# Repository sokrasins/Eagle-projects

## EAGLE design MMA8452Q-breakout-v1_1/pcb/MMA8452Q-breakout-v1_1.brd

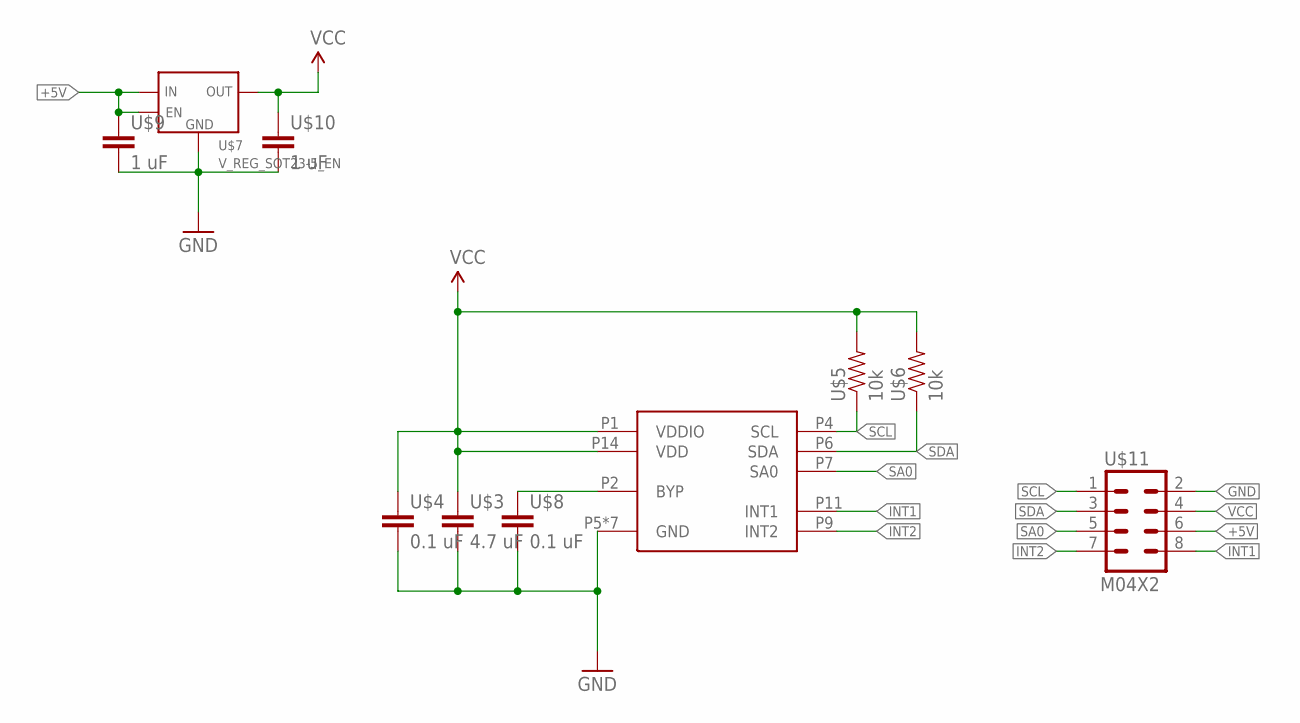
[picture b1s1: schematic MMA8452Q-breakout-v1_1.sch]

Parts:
U$2: MMA_8452; QFN-16-MMA
U$3: 4.7 uF; CAP-0603
U$4, U$8: 0.1 uF; CAP-0603
U$5, U$6: 10k; RES-0603
U$7: V_REG_SOT23-5_EN; SOT23-5
U$9, U$10: 1 uF; CAP-0603
U$11: M04X2; 2X4

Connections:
+5V: U$7.1 (IN), U$7.3 (EN), U$9.1, U$11.6
BYP: U$2.P2 (BYP), U$8.1
GND: U$2.P5 (GND), U$2.P8 (GND), U$2.P10 (GND), U$2.P12 (GND), U$2.P13 (GND), U$2.P15 (GND), U$2.P16 (GND), U$3.2, U$4.2, U$7.2 (GND), U$8.2, U$9.2, U$10.2, U$11.2
INT1: U$2.P11 (INT1), U$11.8
INT2: U$2.P9 (INT2), U$11.7
SA0: U$2.P7 (SA0), U$11.5
SCL: U$2.P4 (SCL), U$5.1, U$11.1
SDA: U$2.P6 (SDA), U$6.1, U$11.3
VCC: U$2.P1 (VDDIO), U$2.P14 (VDD), U$3.1, U$4.1, U$5.2, U$6.2, U$7.5 (OUT), U$10.1, U$11.4

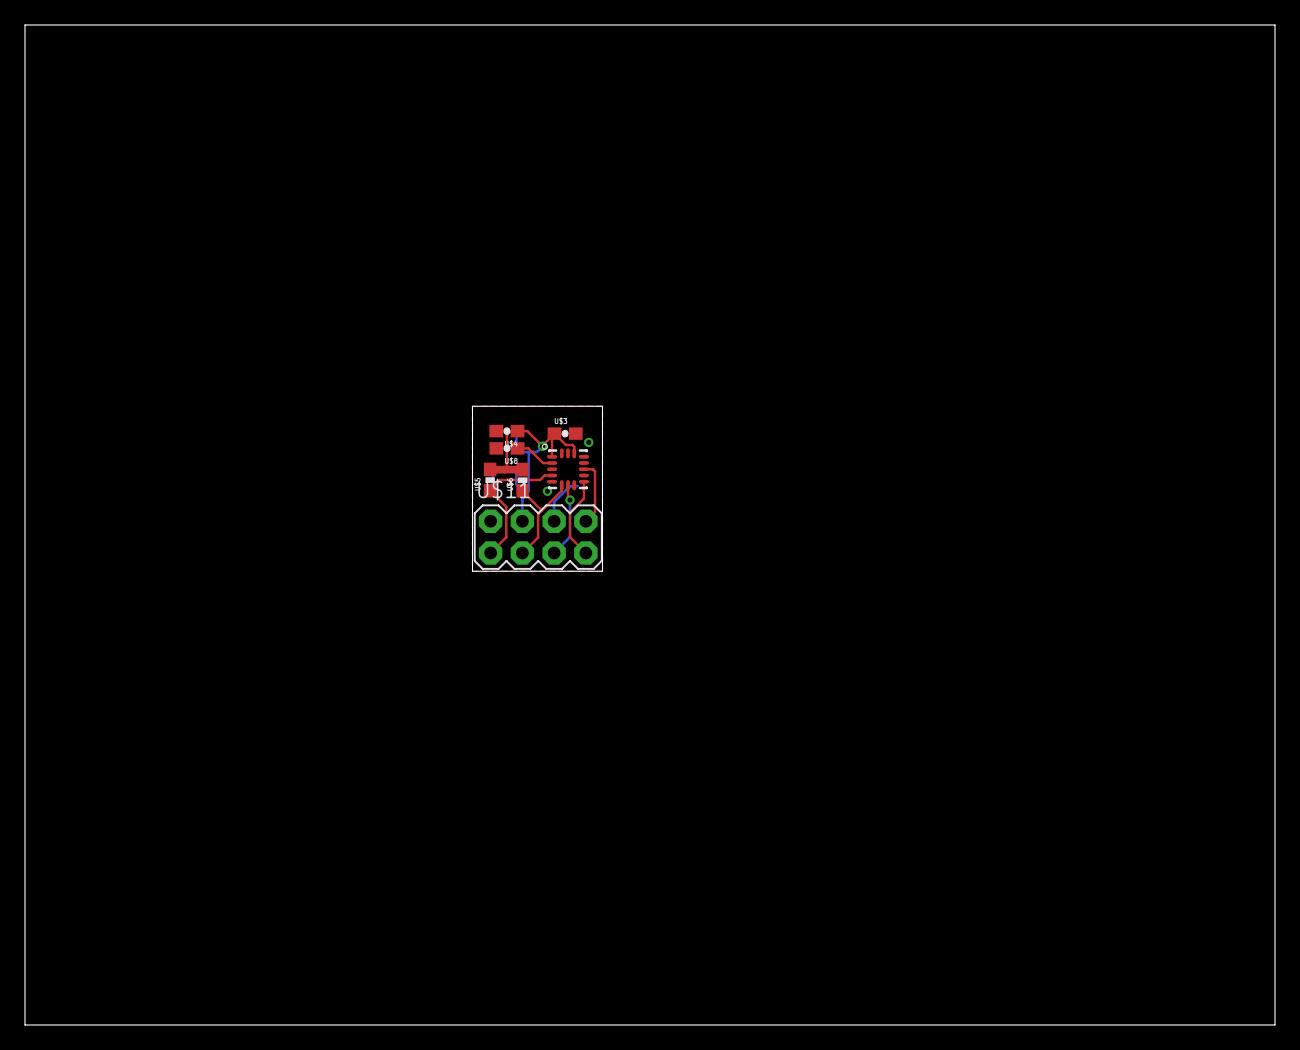
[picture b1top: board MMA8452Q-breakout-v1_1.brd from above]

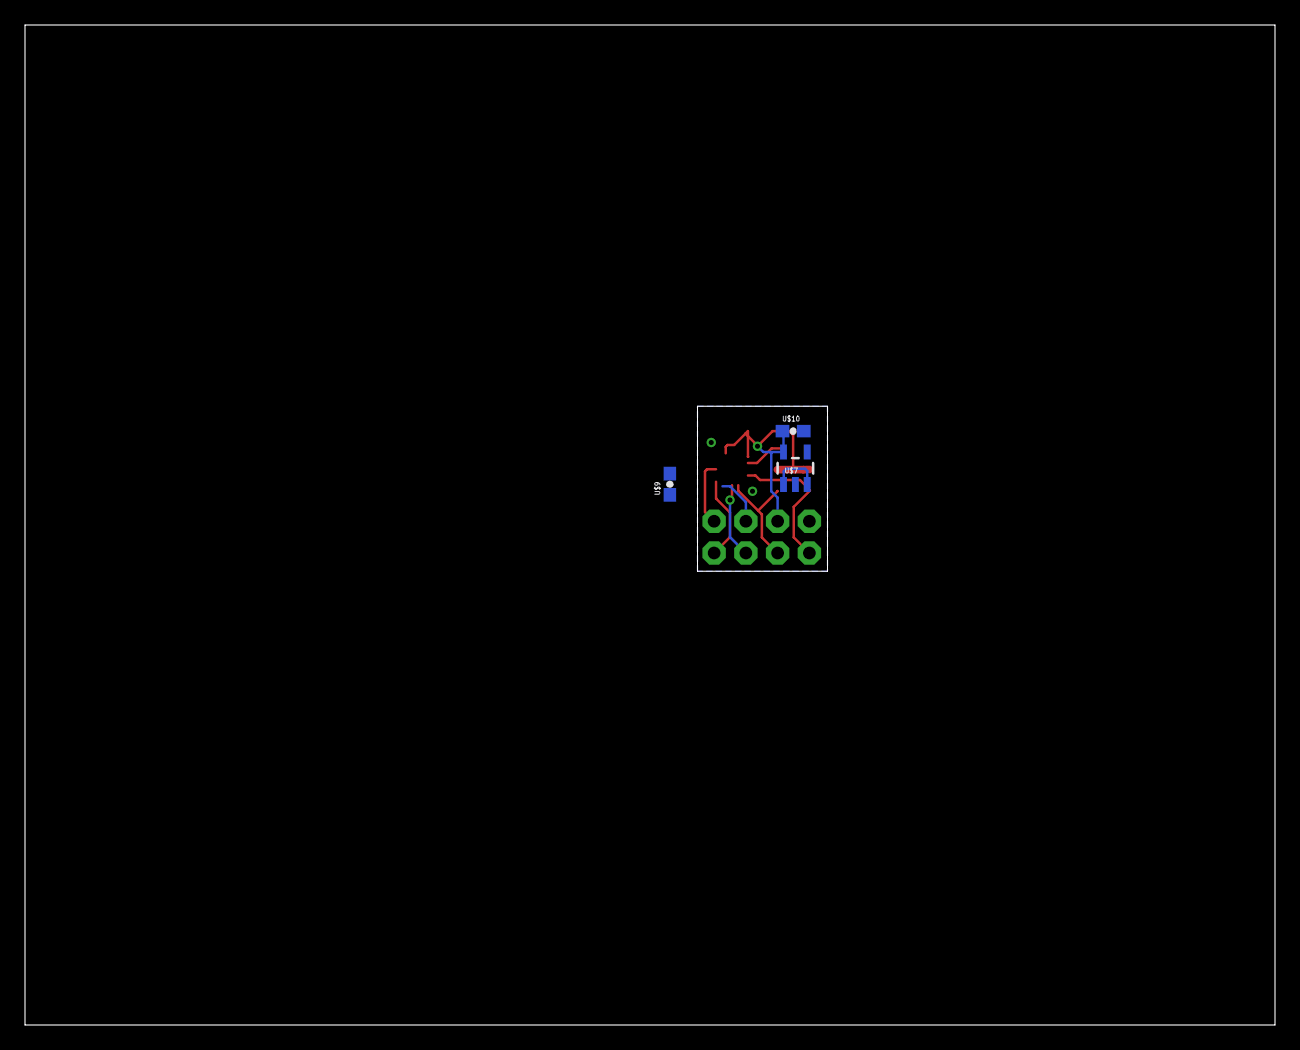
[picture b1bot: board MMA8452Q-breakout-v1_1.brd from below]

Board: 2 copper layers, 100.0 x 80.0 mm, 10 parts (3 on the bottom side), 9 nets.

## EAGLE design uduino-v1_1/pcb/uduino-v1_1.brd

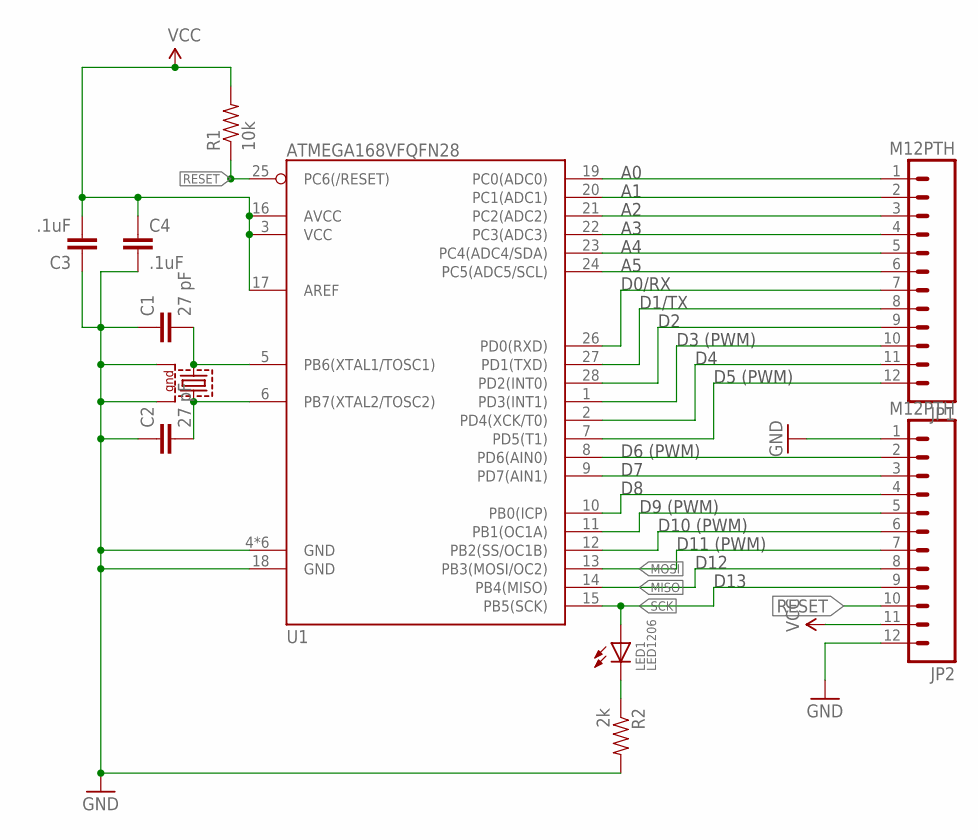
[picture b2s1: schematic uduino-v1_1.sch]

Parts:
C1, C2: 27 pF; CAP-0603
C3, C4: .1uF; CAP-0603
JP1, JP2: M12PTH; 1X12
LED1: LED1206; LED-1206
R1: 10k; RES-0603
R2: 2k; RES-0603
U1: ATMEGA168VFQFN28; VQFN28
X1: CRYSTAL-SMD-7B-SERIES-TXC; CRYSTAL-SMD-7B-SERIES-5X3.2MM

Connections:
GND: C1.1, C2.1, C3.1, C4.2, JP2.1, JP2.12, R2.2, U1.4 (GND), U1.18 (GND), U1.TH (GND), U1.TH@1 (GND), U1.TH@2 (GND), U1.TH@3 (GND), U1.TH@4 (GND), X1.P$2 (2), X1.P$4 (4)
MISO: JP2.8, U1.14 (PB4(MISO))
MOSI: JP2.7, U1.13 (PB3(MOSI/OC2))
unnamed: C1.2, U1.5 (PB6(XTAL1/TOSC1)), X1.P$1 (1)
unnamed: C2.2, U1.6 (PB7(XTAL2/TOSC2)), X1.P$3 (3)
unnamed: LED1.C, R2.1
unnamed: JP2.2, U1.8 (PD6(AIN0))
unnamed: JP2.3, U1.9 (PD7(AIN1))
unnamed: JP1.1, U1.19 (PC0(ADC0))
unnamed: JP1.2, U1.20 (PC1(ADC1))
unnamed: JP1.3, U1.21 (PC2(ADC2))
unnamed: JP1.4, U1.22 (PC3(ADC3))
unnamed: JP1.5, U1.23 (PC4(ADC4/SDA))
unnamed: JP1.6, U1.24 (PC5(ADC5/SCL))
unnamed: JP1.7, U1.26 (PD0(RXD))
unnamed: JP1.8, U1.27 (PD1(TXD))
unnamed: JP1.9, U1.28 (PD2(INT0))
unnamed: JP1.10, U1.1 (PD3(INT1))
unnamed: JP1.11, U1.2 (PD4(XCK/T0))
unnamed: JP1.12, U1.7 (PD5(T1))
unnamed: JP2.4, U1.10 (PB0(ICP))
unnamed: JP2.5, U1.11 (PB1(OC1A))
unnamed: JP2.6, U1.12 (PB2(SS/OC1B))
RESET: JP2.10, R1.1, U1.25 (PC6(/RESET))
SCK: JP2.9, LED1.A, U1.15 (PB5(SCK))
VCC: C3.2, C4.1, JP2.11, R1.2, U1.3 (VCC), U1.16 (AVCC), U1.17 (AREF)

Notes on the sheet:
D0/RX
D1/TX
D3 (PWM)
D5 (PWM)
D6 (PWM)
D9 (PWM)
D10 (PWM)
D11 (PWM)
D12
D13

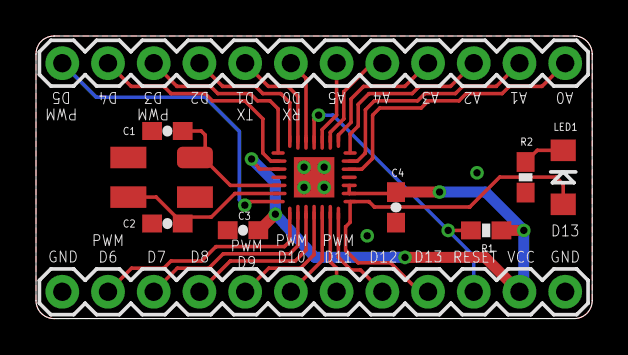
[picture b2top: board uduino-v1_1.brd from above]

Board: 2 copper layers, 30.9 x 15.7 mm, 11 parts (0 on the bottom side), 26 nets.

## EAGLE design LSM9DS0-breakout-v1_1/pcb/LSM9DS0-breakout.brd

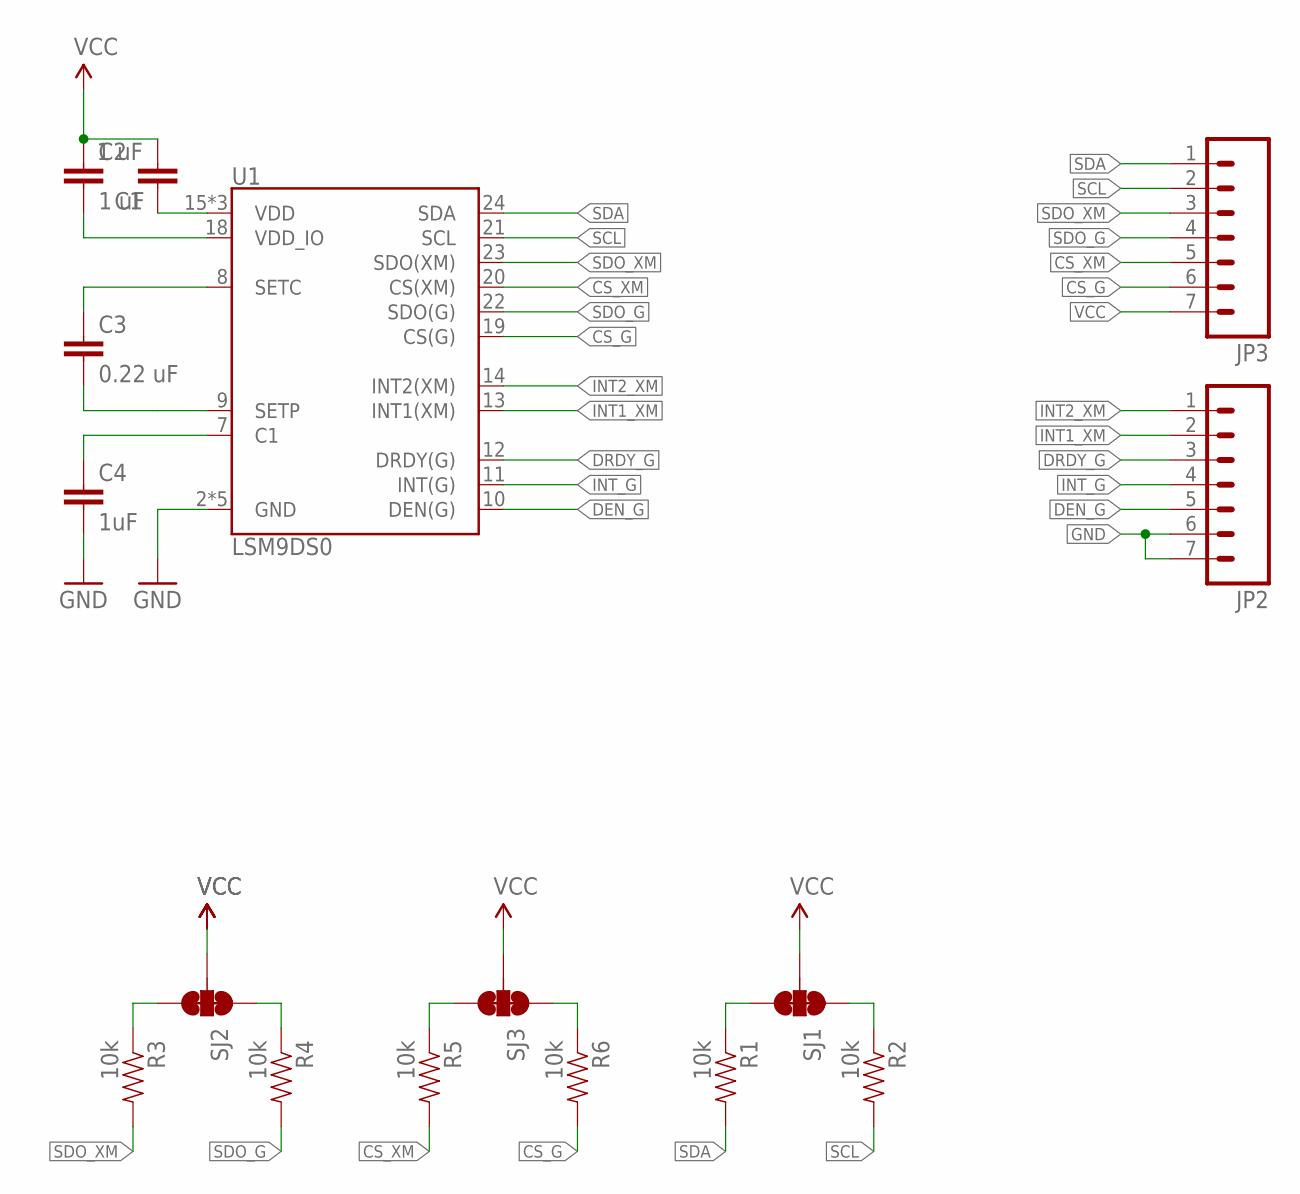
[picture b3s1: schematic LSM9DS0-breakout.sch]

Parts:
C1, C2: 1 uF; 0603-CAP
C3: 0.22 uF; 0603-CAP
C4: 1uF; 0603-CAP
JP2, JP3: M07; 1X07
R1, R2, R3, R4, R5, R6: 10k; 0603-RES
SJ1, SJ2, SJ3: JUMPER-PAD-3-NC_BY_TRACE; PAD-JUMPER-3-3OF3_NC_BY_TRACE_YES_SILK_FULL_BOX
U1: LSM9DS0; LGA-24

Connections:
CS_G: JP3.6, R6.2, U1.19 (CS(G))
CS_XM: JP3.5, R5.2, U1.20 (CS(XM))
DEN_G: JP2.5, U1.10 (DEN(G))
DRDY_G: JP2.3, U1.12 (DRDY(G))
GND: C4.2, JP2.6, JP2.7, U1.2 (GND), U1.3 (GND), U1.4 (GND), U1.5 (GND), U1.6 (GND)
INT1_XM: JP2.2, U1.13 (INT1(XM))
INT2_XM: JP2.1, U1.14 (INT2(XM))
INT_G: JP2.4, U1.11 (INT(G))
unnamed: C3.1, U1.8 (SETC)
unnamed: C3.2, U1.9 (SETP)
unnamed: C4.1, U1.7 (C1)
unnamed: C1.1, U1.15 (VDD), U1.16 (VDD), U1.17 (VDD)
unnamed: C2.2, U1.18 (VDD_IO)
unnamed: R3.1, SJ2.3
unnamed: R4.1, SJ2.1
unnamed: R5.1, SJ3.3
unnamed: R6.1, SJ3.1
unnamed: R1.1, SJ1.3
unnamed: R2.1, SJ1.1
SCL: JP3.2, R2.2, U1.21 (SCL)
SDA: JP3.1, R1.2, U1.24 (SDA)
SDO_G: JP3.4, R4.2, U1.22 (SDO(G))
SDO_XM: JP3.3, R3.2, U1.23 (SDO(XM))
VCC: C1.2, C2.1, JP3.7, SJ1.2, SJ2.2, SJ3.2

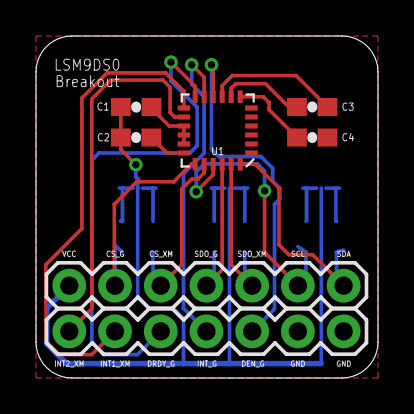
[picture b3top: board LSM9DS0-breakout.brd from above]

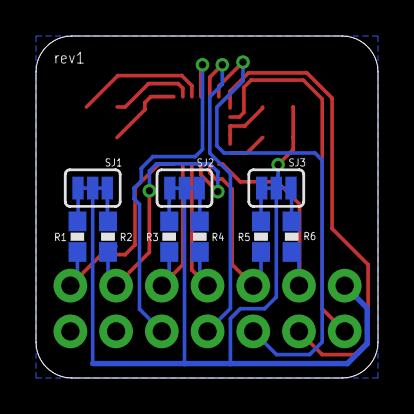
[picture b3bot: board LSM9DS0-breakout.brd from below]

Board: 2 copper layers, 19.0 x 19.0 mm, 16 parts (9 on the bottom side), 24 nets.

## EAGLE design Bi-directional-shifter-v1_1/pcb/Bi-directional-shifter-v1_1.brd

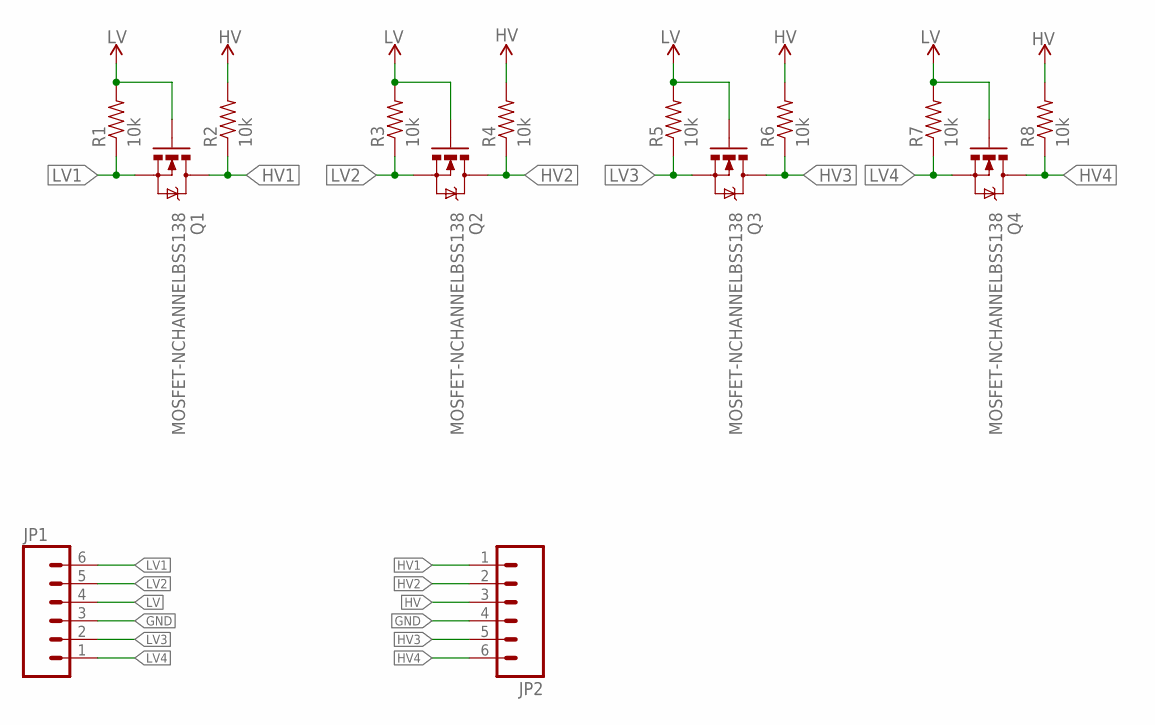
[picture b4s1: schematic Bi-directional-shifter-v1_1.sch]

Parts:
JP1, JP2: M06NO_SILK; 1X06_NO_SILK
Q1, Q2, Q3, Q4: MOSFET-NCHANNELBSS138; SOT23-3
R1, R2, R3, R4, R5, R6, R7, R8: 10k; 0603-RES

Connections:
GND: JP1.3, JP2.4
HV: JP2.3, R2.2, R4.2, R6.2, R8.2
HV1: JP2.1, Q1.3 (D), R2.1
HV2: JP2.2, Q2.3 (D), R4.1
HV3: JP2.5, Q3.3 (D), R6.1
HV4: JP2.6, Q4.3 (D), R8.1
LV: JP1.4, Q1.1 (G), Q2.1 (G), Q3.1 (G), Q4.1 (G), R1.2, R3.2, R5.2, R7.2
LV1: JP1.6, Q1.2 (S), R1.1
LV2: JP1.5, Q2.2 (S), R3.1
LV3: JP1.2, Q3.2 (S), R5.1
LV4: JP1.1, Q4.2 (S), R7.1

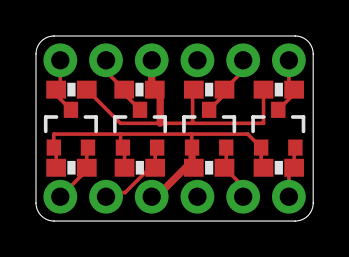
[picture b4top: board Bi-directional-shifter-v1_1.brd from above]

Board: 2 copper layers, 15.4 x 10.3 mm, 14 parts (0 on the bottom side), 11 nets.

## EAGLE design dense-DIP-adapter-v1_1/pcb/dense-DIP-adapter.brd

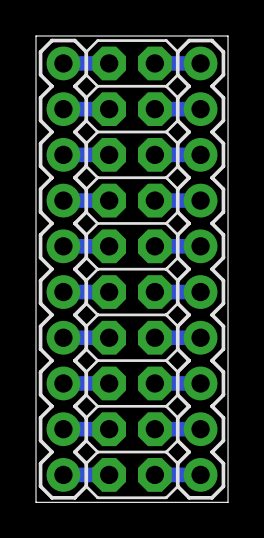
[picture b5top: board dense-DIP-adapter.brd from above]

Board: 2 copper layers, 10.7 x 25.9 mm, 3 parts (0 on the bottom side), 20 nets.

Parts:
JP1, JP2: M10"; 1X10
U$1: M10X2; 2X10

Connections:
unnamed: JP1.10, U$1.1
unnamed: JP1.9, U$1.3
unnamed: JP1.8, U$1.5
unnamed: JP1.7, U$1.7
unnamed: JP1.6, U$1.9
unnamed: JP1.5, U$1.11
unnamed: JP1.4, U$1.13
unnamed: JP1.3, U$1.15
unnamed: JP1.2, U$1.17
unnamed: JP1.1, U$1.19
unnamed: JP2.10, U$1.20
unnamed: JP2.9, U$1.18
unnamed: JP2.8, U$1.16
unnamed: JP2.7, U$1.14
unnamed: JP2.6, U$1.12
unnamed: JP2.5, U$1.10
unnamed: JP2.4, U$1.8
unnamed: JP2.3, U$1.6
unnamed: JP2.2, U$1.4
unnamed: JP2.1, U$1.2

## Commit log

2014-09-16 Added first three pcb projects with datasheets, pcb, and gerbs.
2014-10-05 First commit, with pcb, gerbs, and datasheets
2014-10-06 First commit, started psb, added datasheet

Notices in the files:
parts and their libraries:
SparkFun-DiscreteSemi: Licensing: Creative Commons ShareAlike 4.0 International - https://creativecommons.org/licenses/by-sa/4.0
SparkFun: Licensing: CC v3.0 Share-Alike You are welcome to use this library for commercial purposes.
